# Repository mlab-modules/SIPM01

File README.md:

<!--- PrjInfo ---> <!--- Please remove this line after manually editing --->
<!--- 00a56be08b96043df9e37d6aff7b6990 --->
<!--- Created:2019-02-18 14:39:35.935286: --->
<!--- Author:: --->
<!--- AuthorEmail:: --->
<!--- Tags:: --->
<!--- Ust:: --->
<!--- Label --->
<!--- ELabel --->
<!--- Name:SIPM01A: --->
# SIPM01A - Silicon photomultiplier analog front end

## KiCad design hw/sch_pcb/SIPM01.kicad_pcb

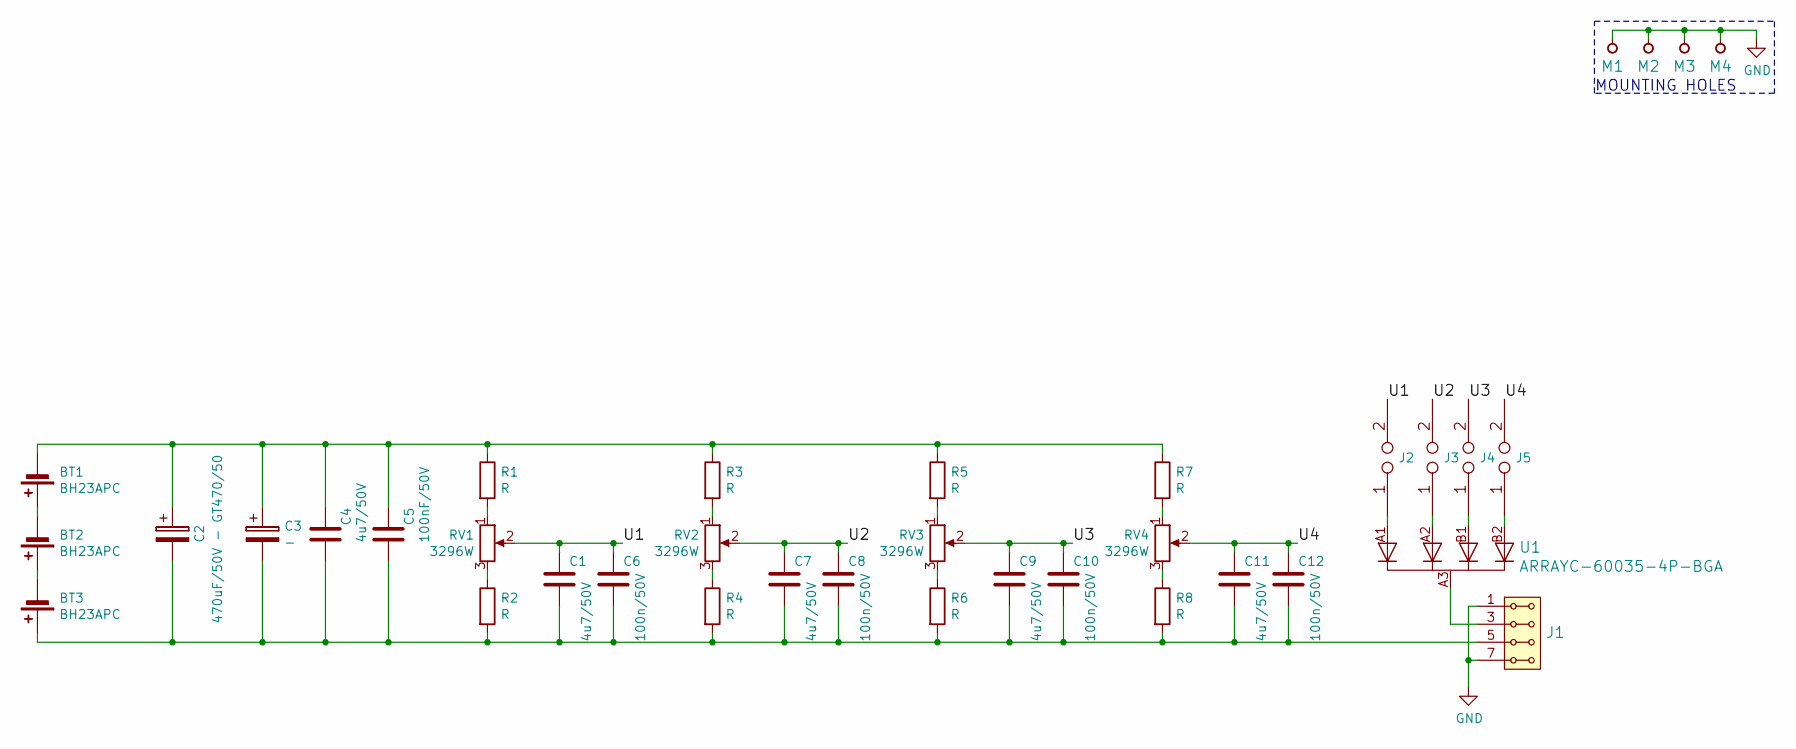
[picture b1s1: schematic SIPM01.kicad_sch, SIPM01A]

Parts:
BT1, BT2, BT3: BH23APC
C1, C4, C7, C9, C11: 4u7/50V; SMD-0805
C2: 470uF/50V - GT470/50; CP_Radial_D10.0mm_P5.00mm
C3: -; TantalC_SizeC_Reflow
C5: 100nF/50V; SMD-0805
C6, C8, C10, C12: 100n/50V; SMD-0805
J1: HEADER_2x04_PARALLEL; Straight_2x04
J2, J3, J4, J5: JUMP2_2x1; Zkrat
M1, M2, M3, M4: HOLE; MountingHole_3mm
R1, R2, R3, R4, R5, R6, R7, R8: R; SMD-0805
RV1, RV2, RV3, RV4: 3296W; Potentiometer_Bourns_3296W_Vertical
U1: ARRAYC-60035-4P-BGA; ArrayC-60035-4P-BGA

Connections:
/U1: C1.1, C6.1, J2.2, RV1.2
/U2: C7.1, C8.1, J3.2, RV2.2
/U3: C9.1, C10.1, J4.2, RV3.2
/U4: C11.1, C12.1, J5.2, RV4.2
GND: J1.1, J1.2, J1.7, J1.8, M1.1, M2.1, M3.1, M4.1
unnamed: BT1.1 (+), BT2.2 (-)
unnamed: BT1.2 (-), C2.1, C3.1, C4.1, C5.1, R1.1, R3.1, R5.1, R7.1
unnamed: BT2.1 (+), BT3.2 (-)
unnamed: BT3.1 (+), C1.2, C2.2, C3.2, C4.2, C5.2, C6.2, C7.2, C8.2, C9.2, C10.2, C11.2, C12.2, J1.5, J1.6, R2.2, R4.2, R6.2, R8.2
unnamed: J1.3, J1.4, U1.A3, U1.B3, U1.C1, U1.C2, U1.C3
unnamed: J2.1, U1.A1
unnamed: J3.1, U1.A2
unnamed: J4.1, U1.B1
unnamed: J5.1, U1.B2
unnamed: R1.2, RV1.1
unnamed: R2.1, RV1.3
unnamed: R3.2, RV2.1
unnamed: R4.1, RV2.3
unnamed: R5.2, RV3.1
unnamed: R6.1, RV3.3
unnamed: R7.2, RV4.1
unnamed: R8.1, RV4.3

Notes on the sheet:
MOUNTING HOLES

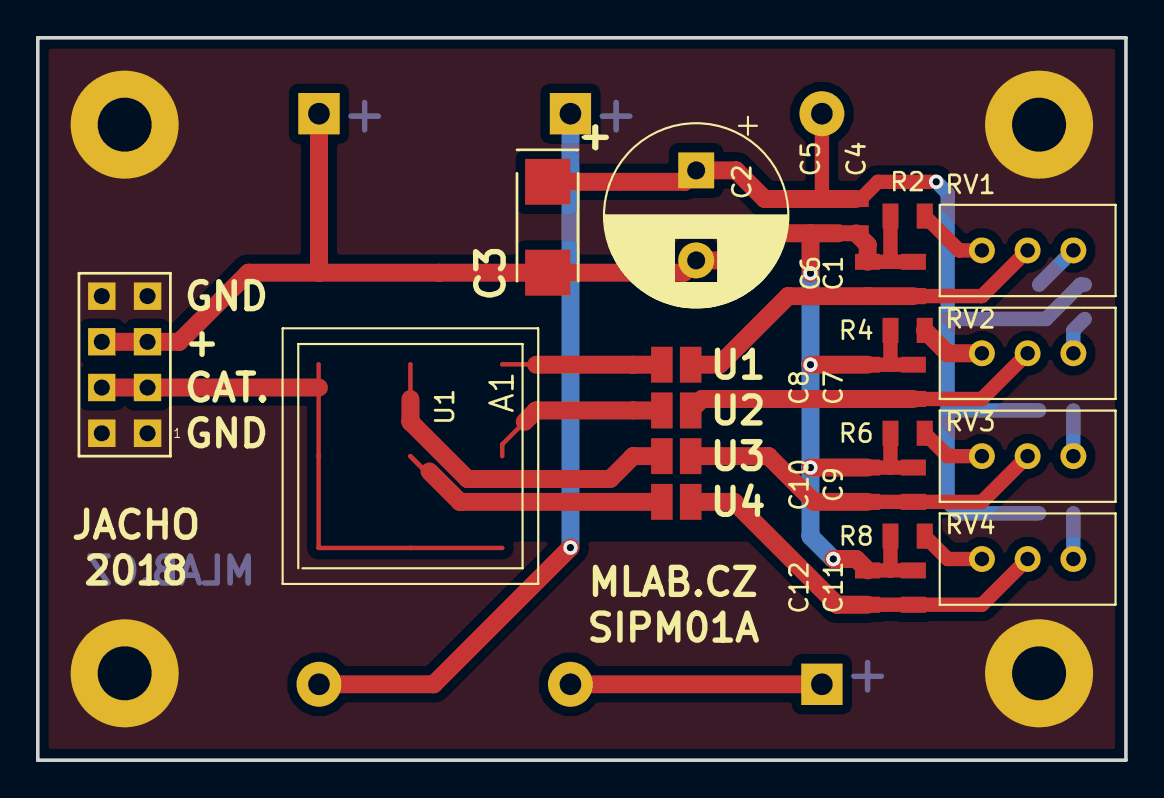
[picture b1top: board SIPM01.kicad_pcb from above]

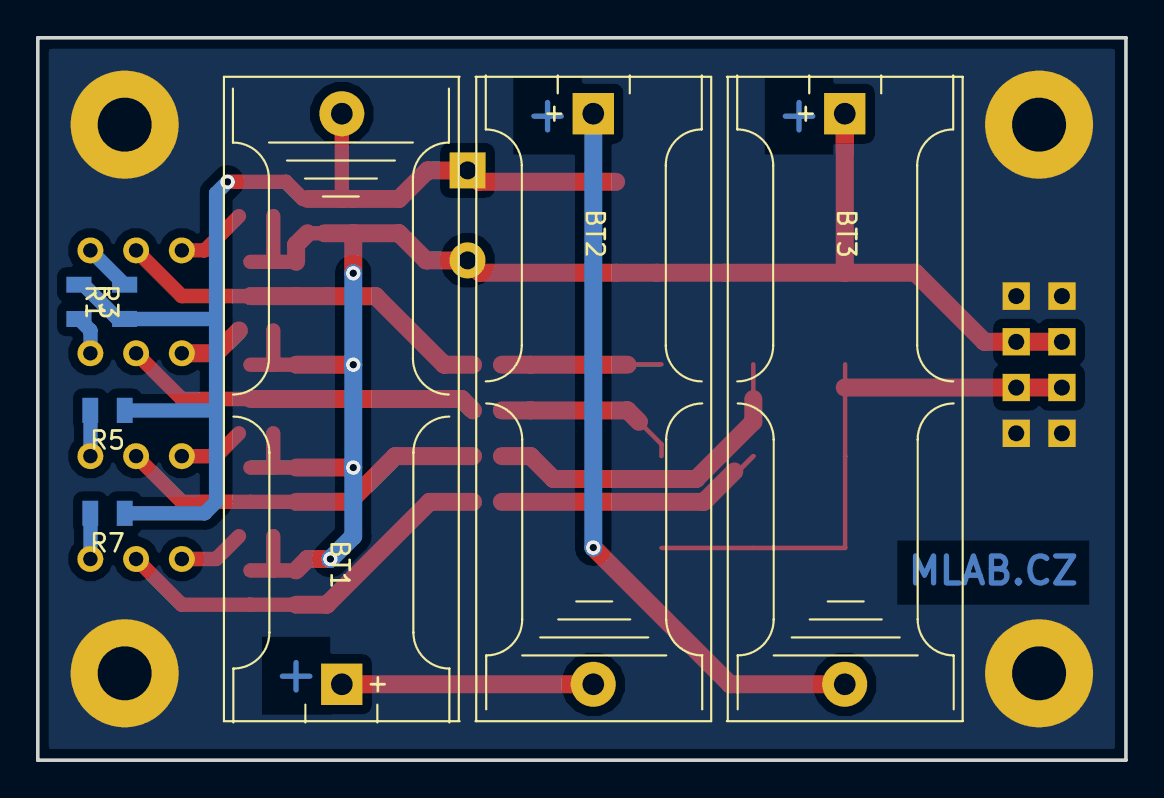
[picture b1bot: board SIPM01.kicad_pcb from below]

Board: 2 copper layers, 60.5 x 40.1 mm, 37 parts (7 on the bottom side), 22 nets.

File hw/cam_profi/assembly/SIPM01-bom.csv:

Component,Description,Part,References,Value,Footprint,Quantity Per PCB,Datasheet
1,Single-cell battery,Battery_Cell,BT1BT2BT3,BH23APC,BH23APC,3,~
2,,CP-Device,C3,-,TantalC_SizeC_Reflow,1,
3,Unpolarized capacitor,C,C6C8C10C12,100n/50V,SMD-0805,4,~
4,Unpolarized capacitor,C,C5,100nF/50V,SMD-0805,1,~
5,,CP-Device,C2,470uF/50V - GT470/50,CP_Radial_D10.0mm_P5.00mm,1,
6,Unpolarized capacitor,C,C1C4C7C9C11,4u7/50V,SMD-0805,5,~
7,"2x04 2.54 mm pitch header, 2 pins next to each other are connected",HEADER_2x04_PARALLEL,J1,HEADER_2x04_PARALLEL,Straight_2x04,1,
8,MLAB modified doubled pinheader connector,JUMP2_2x1,J2J3J4J5,JUMP2_2x1,Zkrat,4,
9,Resistor,R,R1R2R3R4R5R6R7R8,R,SMD-0805,8,~
10,,R_POT-Device,RV1RV2RV3RV4,3296W,Potentiometer_Bourns_3296W_Vertical,4,
11,,ARRAYC-60035-4P-BGA,U1,ARRAYC-60035-4P-BGA,ArrayC-60035-4P-BGA,1,

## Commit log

2022-04-06 automated commit; add github actions
2023-04-01 Adding force option to enable splitting in not fresh copy of Modules repository.
2023-05-25 Update metadata files
2023-05-28 Update workflow files
2023-09-16 Update status
2024-07-04 Update to Kicadv7.
2024-07-04 Update actions products
2024-07-04 Update readme.
